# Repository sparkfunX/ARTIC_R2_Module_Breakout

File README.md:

# A Thing Plus Breakout for the ARGOS ARTIC R2 Castellated Module

**SPX-17855**

## Repository Contents

- [**/Hardware**](./Hardware) - Eagle PCB, SCH and LBR design files
- [**LICENSE.md**](./LICENSE,md) - contains the licence information

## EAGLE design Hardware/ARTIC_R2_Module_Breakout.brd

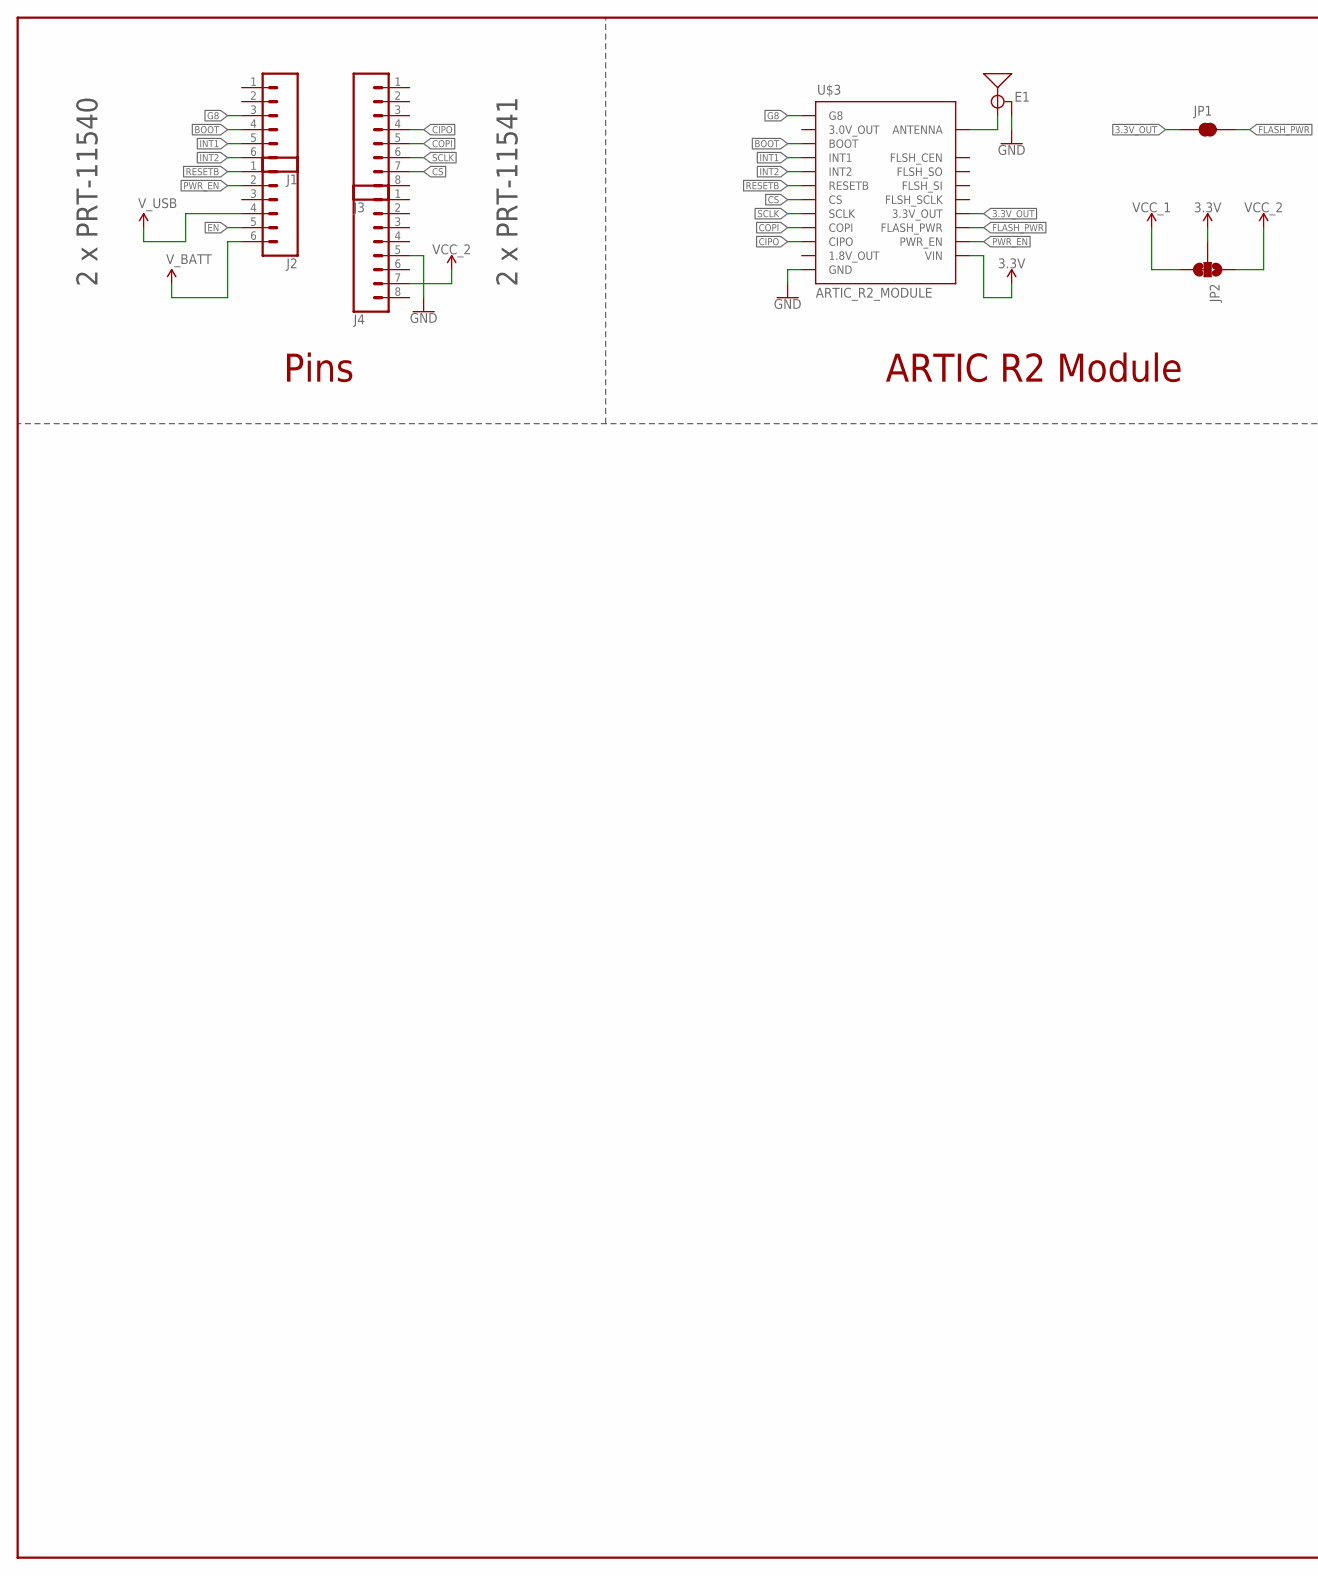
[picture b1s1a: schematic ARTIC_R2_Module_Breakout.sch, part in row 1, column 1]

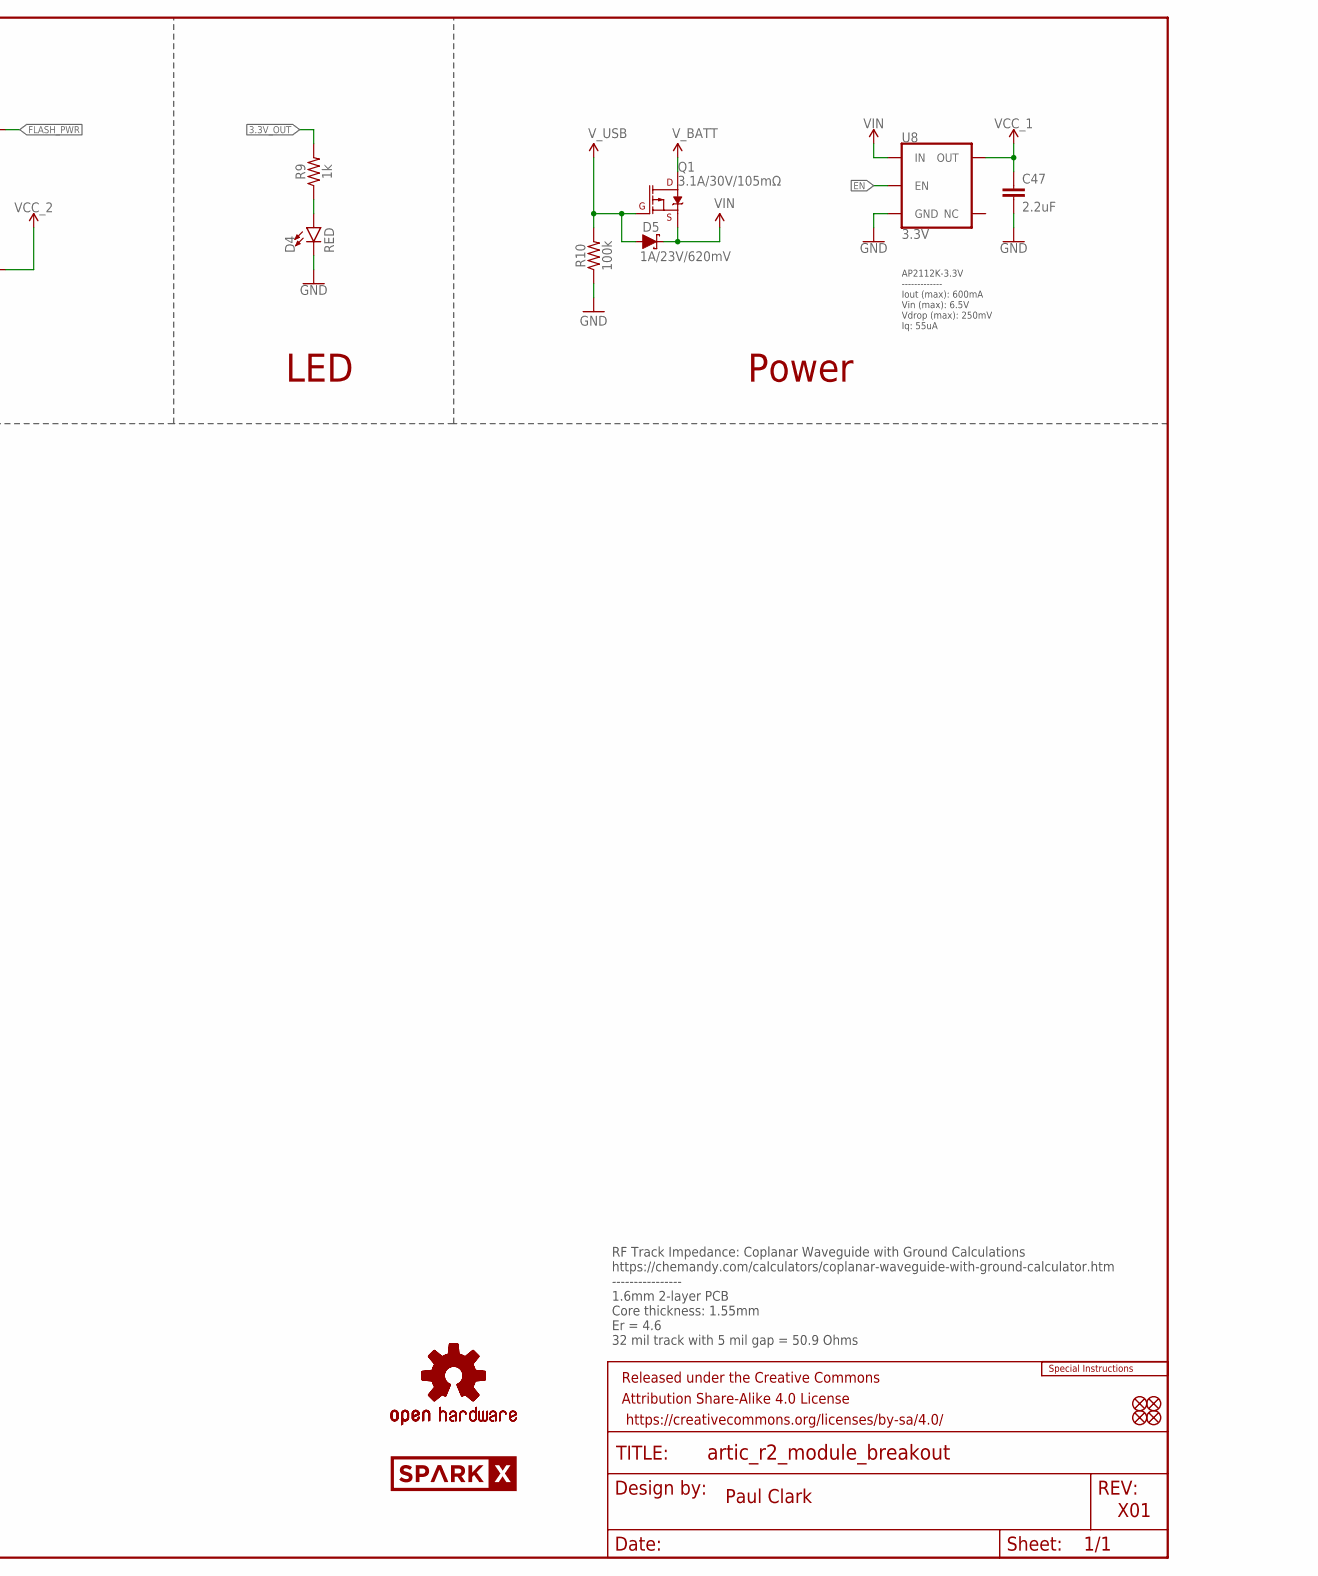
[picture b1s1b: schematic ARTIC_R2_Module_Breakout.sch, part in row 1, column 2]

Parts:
C47: 2.2uF; 0402-TIGHT
D4: RED; LED-0603
D5: 1A/23V/620mV; SOD-323
E1: ANTENNA-SMA-GROUNDEDEDGE_SMA_SMD; SMA-EDGE-SMD
FD1, FD2, FD3, FD4: FIDUCIAL1X2; FIDUCIAL-1X2
FRAME1: FRAME-LEDGER; CREATIVE_COMMONS
J1, J2: CONN_06SMD_MALE; 1X06_SMD_MALE
J3, J4: CONN_08SMD-MALE; 1X08_SMD_MALE
JP1: JUMPER-SMT_2_NC_TRACE_SILK; SMT-JUMPER_2_NC_TRACE_SILK
JP2: JUMPER-SMT_3_1-NC_TRACE_SILK; SMT-JUMPER_3_1-NC_TRACE_SILK
LOGO1: SPECIAL_INSTRUCTIONS-ORDERING; ORDERING_INSTRUCTIONS
LOGO2, LOGO3: OSHW-LOGOS; OSHW-LOGO-S
Q1: 3.1A/30V/105mΩ; SOT23-3
R9: 1k; 0402-TIGHT
R10: 100k; 0402-TIGHT
SPARKX2: SPARKX-LOGO4; SPARKX-MEDIUM
U8: 3.3V; SOT23-5
U$3: ARTIC_R2_MODULE

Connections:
3.3V: JP2.2, U$3.14 (VIN)
3.3V_OUT: JP1.1, R9.2, U$3.17 (3.3V_OUT)
ANTENNA: E1.SIG (SIGNAL), U$3.23 (ANTENNA)
BOOT: J1.4, U$3.3 (BOOT)
CIPO: J3.4, U$3.10 (CIPO)
COPI: J3.5, U$3.9 (COPI)
CS: J3.7, U$3.7 (CS)
EN: J2.5, U8.3 (EN)
FLASH_PWR: JP1.2, U$3.16 (FLASH_PWR)
G8: J1.3, U$3.1 (G8)
GND: C47.2, D4.C, E1.GND@0 (GND), E1.GND@1 (GND), J4.5, R10.1, U8.2 (GND), U$3.12 (GND), U$3.13 (GND), U$3.22 (GND), U$3.24 (GND)
INT1: J1.5, U$3.4 (INT1)
INT2: J1.6, U$3.5 (INT2)
unnamed: D4.A, R9.1
PWR_EN: J2.2, U$3.15 (PWR_EN)
RESETB: J2.1, U$3.6 (RESETB)
SCLK: J3.6, U$3.8 (SCLK)
VCC_1: C47.1, JP2.3, U8.5 (OUT)
VCC_2: J4.7, JP2.1
VIN: D5.C, Q1.2 (S), U8.1 (IN)
V_BATT: J2.6, Q1.3 (D)
V_USB: D5.A, J2.4, Q1.1 (G), R10.2

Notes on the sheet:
Paul Clark
X01
ARTIC R2 Module
Pins
RF Track Impedance: Coplanar Waveguide with Ground Calculations https://chemandy.com/calculators/coplanar-waveguide-with-ground-calculator.htm ---------------- 1.6mm 2-layer PCB Core thickness: 1.55mm Er = 4.6 32 mil track with 5 mil gap = 50.9 Ohms
LED
2 x PRT-11541
2 x PRT-11540
AP2112K-3.3V ------------- Iout (max): 600mA Vin (max): 6.5V Vdrop (max): 250mV Iq: 55uA
Power

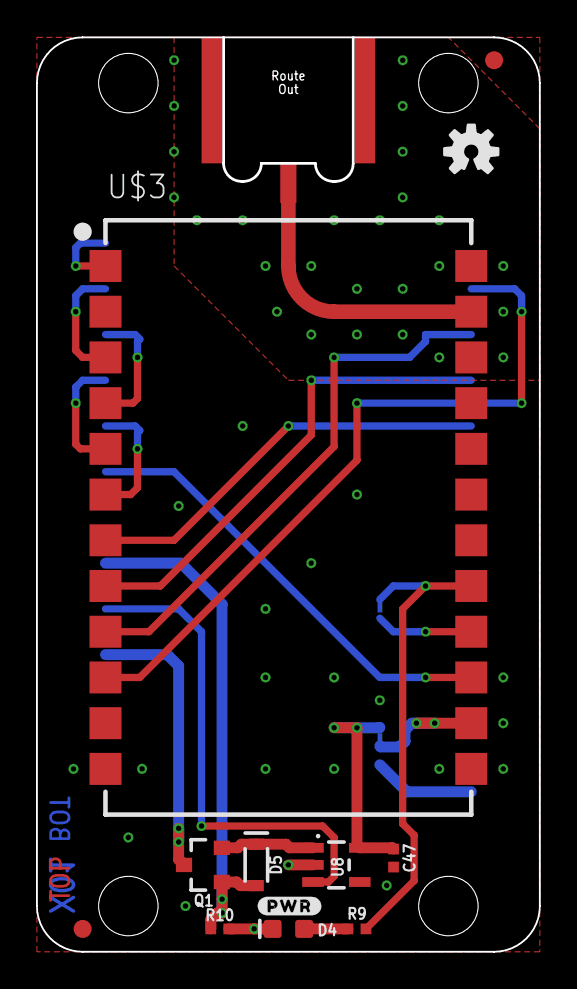
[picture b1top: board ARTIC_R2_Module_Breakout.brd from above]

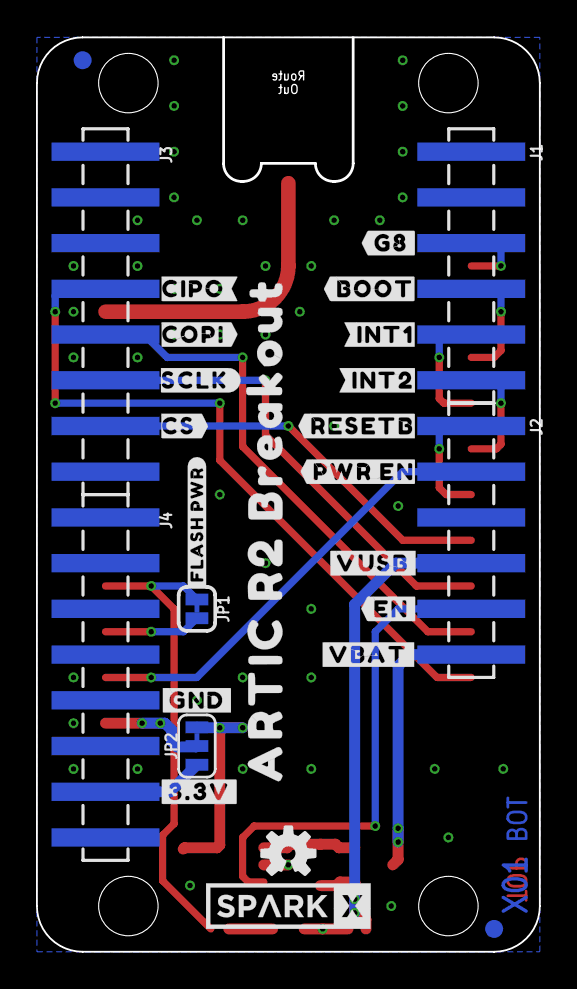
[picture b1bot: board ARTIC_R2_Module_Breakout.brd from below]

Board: 4 copper layers, 27.9 x 50.8 mm, 42 parts (27 on the bottom side), 22 nets.

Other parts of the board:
U$1: #GND#0
U$2: #3#3V#0
U$4: #FLASH_PWR#0
U$5: #VBAT#0
U$6: #G8#0
U$7: #EN#0
U$8: #VUSB#0
U$9: CIPO#0
U$12: COPI#0
U$14: SCLK#0
U$16: CS#0
U$18: #RESETB0
U$19: #PWR_EN0
U$24: #BOOT0
U$25: #INT10
U$26: #INT20
U$28: #PWR#0
U$29: ARTIC_R2_BREAKOUT0

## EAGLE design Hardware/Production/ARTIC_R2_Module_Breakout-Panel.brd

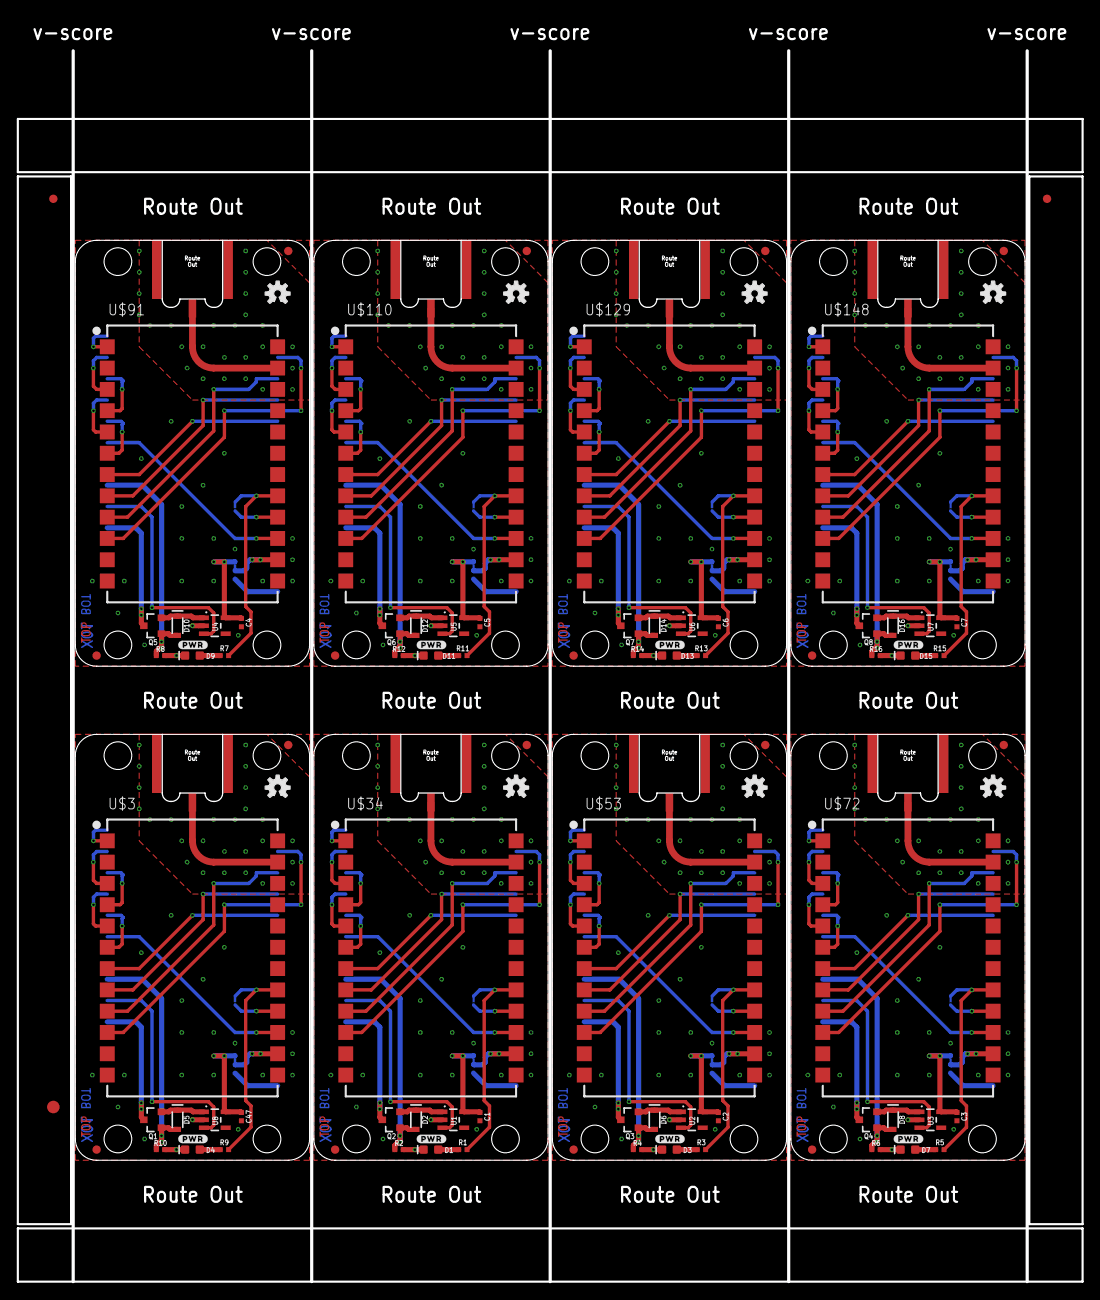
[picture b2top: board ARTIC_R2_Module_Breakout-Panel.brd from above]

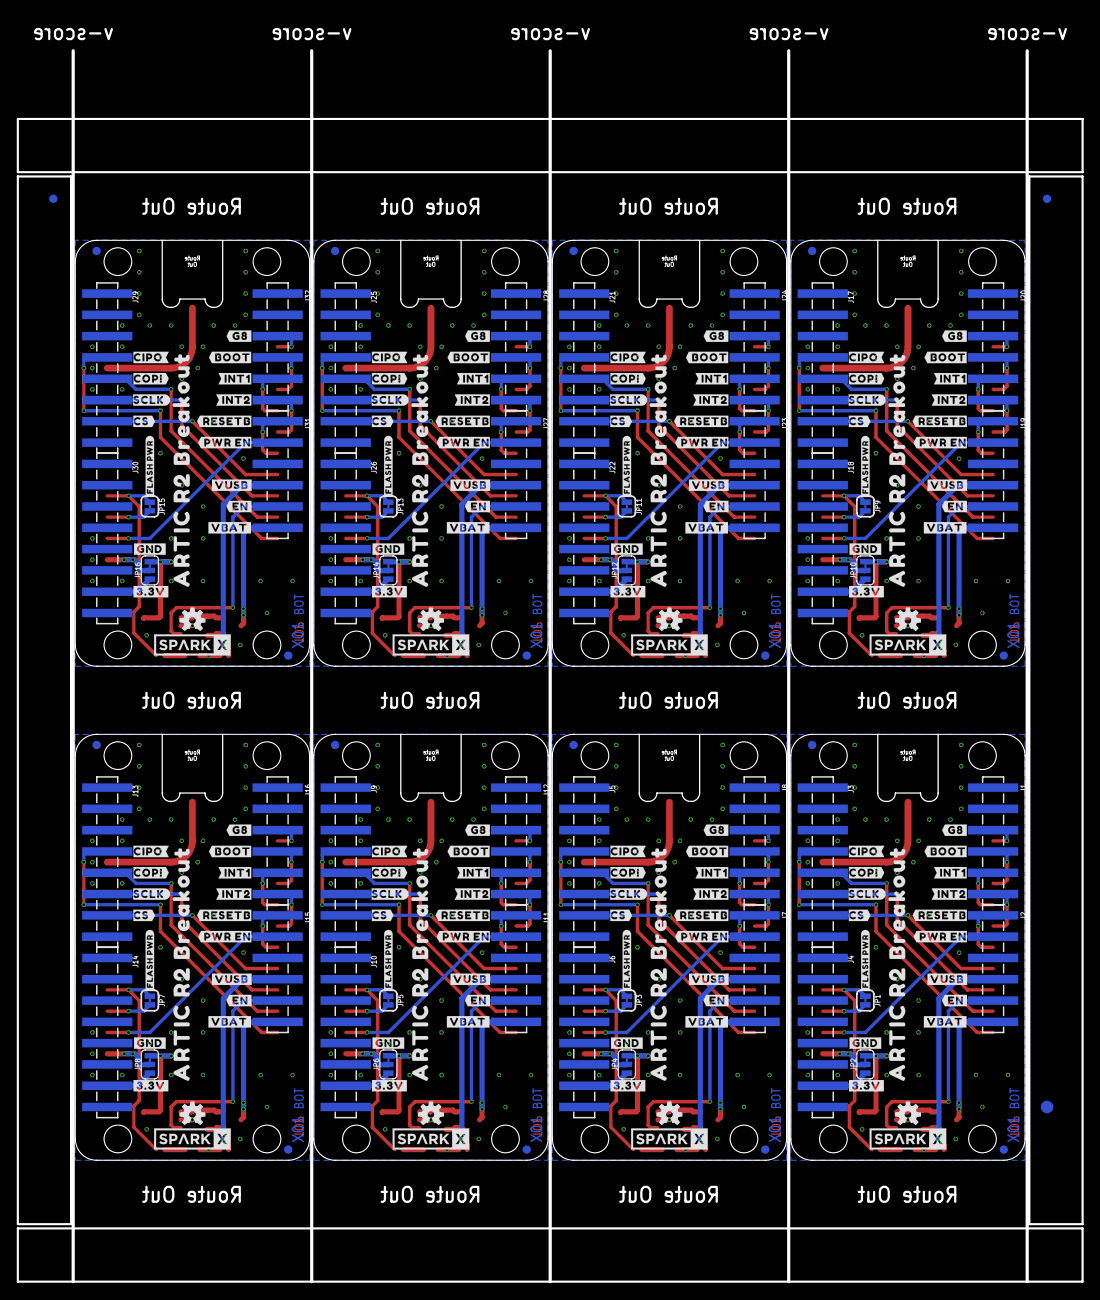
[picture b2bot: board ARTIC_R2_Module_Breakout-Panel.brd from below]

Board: 4 copper layers, 126.9 x 150.7 mm, 326 parts (219 on the bottom side), 176 nets.

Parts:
C1, C2, C3, C4, C5, C6, C7, C47: 2.2uF; 0402-TIGHT
D1, D3, D4, D7, D9, D11, D13, D15: RED; LED-0603
D2, D5, D6, D8, D10, D12, D14, D16: 1A/23V/620mV; SOD-323
E1, E2, E3, E4, E5, E6, E7, E8: ANTENNA-SMA-GROUNDEDEDGE_SMA_SMD; SMA-EDGE-SMD
E$1, E$2, E$3, E$4: FIDUCIAL-1X2
E$5, E$6: FIDUCIAL-1.5X3
FD1, FD2, FD3, FD4, FD5, FD6, FD7, FD8, FD9, FD10, FD11, FD12, FD13, FD14, FD15, FD16, FD17, FD18, FD19, FD20, FD21, FD22, FD23, FD24, FD25, FD26, FD27, FD28, FD29, FD30, FD31, FD32: FIDUCIAL1X2; FIDUCIAL-1X2
J1, J2, J7, J8, J11, J12, J15, J16, J19, J20, J23, J24, J27, J28, J31, J32: 1X06_SMD_MALE
J3, J4, J5, J6, J9, J10, J13, J14, J17, J18, J21, J22, J25, J26, J29, J30: 1X08_SMD_MALE
JP1, JP3, JP5, JP7, JP9, JP11, JP13, JP15: JUMPER-SMT_2_NC_TRACE_SILK; SMT-JUMPER_2_NC_TRACE_SILK
JP2, JP4, JP6, JP8, JP10, JP12, JP14, JP16: JUMPER-SMT_3_1-NC_TRACE_SILK; SMT-JUMPER_3_1-NC_TRACE_SILK
LOGO1, LOGO2, LOGO3, LOGO4, LOGO5, LOGO6, LOGO7, LOGO8, LOGO9, LOGO10, LOGO11, LOGO12, LOGO13, LOGO14, LOGO15, LOGO16: OSHW-LOGOS; OSHW-LOGO-S
Q1, Q2, Q3, Q4, Q5, Q6, Q7, Q8: 3.1A/30V/105mΩ; SOT23-3
R1, R3, R5, R7, R9, R11, R13, R15: 1k; 0402-TIGHT
R2, R4, R6, R8, R10, R12, R14, R16: 100k; 0402-TIGHT
SPARKX1, SPARKX2, SPARKX3, SPARKX4, SPARKX5, SPARKX6, SPARKX7, SPARKX8: SPARKX-LOGO4; SPARKX-MEDIUM
U1, U2, U3, U4, U5, U6, U7, U8: 3.3V; SOT23-5
U$1, U$32, U$51, U$70, U$89, U$108, U$127, U$146: #GND#0
U$2, U$33, U$52, U$71, U$90, U$109, U$128, U$147: #3#3V#0
U$3, U$34, U$53, U$72, U$91, U$110, U$129, U$148: ARTIC_R2_MODULE
U$4, U$38, U$57, U$76, U$95, U$114, U$133, U$152: #FLASH_PWR#0
U$5, U$35, U$54, U$73, U$92, U$111, U$130, U$149: #VBAT#0
U$6, U$31, U$50, U$69, U$88, U$107, U$126, U$145: #G8#0
U$7, U$36, U$55, U$74, U$93, U$112, U$131, U$150: #EN#0
U$8, U$37, U$56, U$75, U$94, U$113, U$132, U$151: #VUSB#0
U$9, U$10, U$39, U$58, U$77, U$96, U$115, U$134: CIPO#0
U$11, U$12, U$40, U$59, U$78, U$97, U$116, U$135: COPI#0
U$13, U$14, U$41, U$60, U$79, U$98, U$117, U$136: SCLK#0
U$15, U$16, U$42, U$61, U$80, U$99, U$118, U$137: CS#0
U$17, U$24, U$43, U$62, U$81, U$100, U$119, U$138: #BOOT0
U$18, U$20, U$44, U$63, U$82, U$101, U$120, U$139: #RESETB0
U$19, U$21, U$45, U$64, U$83, U$102, U$121, U$140: #PWR_EN0
U$22, U$26, U$46, U$65, U$84, U$103, U$122, U$141: #INT20
U$23, U$25, U$47, U$66, U$85, U$104, U$123, U$142: #INT10
U$27, U$28, U$48, U$67, U$86, U$105, U$124, U$143: #PWR#0
U$29, U$30, U$49, U$68, U$87, U$106, U$125, U$144: ARTIC_R2_BREAKOUT0

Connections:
3.3V: JP2.2, U$3.14
3.3V1: JP4.2, U$34.14
3.3V2: JP6.2, U$53.14
3.3V3: JP8.2, U$72.14
3.3V4: JP10.2, U$91.14
3.3V5: JP12.2, U$110.14
3.3V6: JP14.2, U$129.14
3.3V7: JP16.2, U$148.14
3.3V_OUT: JP1.1, R9.2, U$3.17
3.3V_OUT1: JP3.1, R1.2, U$34.17
3.3V_OUT2: JP5.1, R3.2, U$53.17
3.3V_OUT3: JP7.1, R5.2, U$72.17
3.3V_OUT4: JP9.1, R7.2, U$91.17
3.3V_OUT5: JP11.1, R11.2, U$110.17
3.3V_OUT6: JP13.1, R13.2, U$129.17
3.3V_OUT7: JP15.1, R15.2, U$148.17
ANTENNA: E1.SIG, U$3.23
ANTENNA1: E2.SIG, U$34.23
ANTENNA2: E3.SIG, U$53.23
ANTENNA3: E4.SIG, U$72.23
ANTENNA4: E5.SIG, U$91.23
ANTENNA5: E6.SIG, U$110.23
ANTENNA6: E7.SIG, U$129.23
ANTENNA7: E8.SIG, U$148.23
BOOT: J1.4, U$3.3
BOOT1: J8.4, U$34.3
BOOT2: J12.4, U$53.3
BOOT3: J16.4, U$72.3
BOOT4: J20.4, U$91.3
BOOT5: J24.4, U$110.3
BOOT6: J28.4, U$129.3
BOOT7: J32.4, U$148.3
CIPO: J3.4, U$3.10
CIPO1: J5.4, U$34.10
CIPO2: J9.4, U$53.10
CIPO3: J13.4, U$72.10
CIPO4: J17.4, U$91.10
CIPO5: J21.4, U$110.10
CIPO6: J25.4, U$129.10
CIPO7: J29.4, U$148.10
COPI: J3.5, U$3.9
COPI1: J5.5, U$34.9
COPI2: J9.5, U$53.9
COPI3: J13.5, U$72.9
COPI4: J17.5, U$91.9
COPI5: J21.5, U$110.9
COPI6: J25.5, U$129.9
COPI7: J29.5, U$148.9
CS: J3.7, U$3.7
CS1: J5.7, U$34.7
CS2: J9.7, U$53.7
CS3: J13.7, U$72.7
CS4: J17.7, U$91.7
CS5: J21.7, U$110.7
CS6: J25.7, U$129.7
CS7: J29.7, U$148.7
EN: J2.5, U8.3
EN1: J7.5, U1.3
EN2: J11.5, U2.3
EN3: J15.5, U3.3
EN4: J19.5, U4.3
EN5: J23.5, U5.3
EN6: J27.5, U6.3
EN7: J31.5, U7.3
FLASH_PWR: JP1.2, U$3.16
FLASH_PWR1: JP3.2, U$34.16
FLASH_PWR2: JP5.2, U$53.16
FLASH_PWR3: JP7.2, U$72.16
FLASH_PWR4: JP9.2, U$91.16
FLASH_PWR5: JP11.2, U$110.16
FLASH_PWR6: JP13.2, U$129.16
FLASH_PWR7: JP15.2, U$148.16
G1: J8.3, U$34.1
G2: J12.3, U$53.1
G3: J16.3, U$72.1
G4: J20.3, U$91.1
G5: J24.3, U$110.1
G6: J28.3, U$129.1
G7: J32.3, U$148.1
G8: J1.3, U$3.1
GND: C47.2, D4.C, E1.GND@0, E1.GND@1, J4.5, R10.1, U8.2, U$3.12, U$3.13, U$3.22, U$3.24
GND1: C1.2, D1.C, E2.GND@0, E2.GND@1, J6.5, R2.1, U1.2, U$34.12, U$34.13, U$34.22, U$34.24
GND2: C2.2, D3.C, E3.GND@0, E3.GND@1, J10.5, R4.1, U2.2, U$53.12, U$53.13, U$53.22, U$53.24
GND3: C3.2, D7.C, E4.GND@0, E4.GND@1, J14.5, R6.1, U3.2, U$72.12, U$72.13, U$72.22, U$72.24
GND4: C4.2, D9.C, E5.GND@0, E5.GND@1, J18.5, R8.1, U4.2, U$91.12, U$91.13, U$91.22, U$91.24
GND5: C5.2, D11.C, E6.GND@0, E6.GND@1, J22.5, R12.1, U5.2, U$110.12, U$110.13, U$110.22, U$110.24
GND6: C6.2, D13.C, E7.GND@0, E7.GND@1, J26.5, R14.1, U6.2, U$129.12, U$129.13, U$129.22, U$129.24
GND7: C7.2, D15.C, E8.GND@0, E8.GND@1, J30.5, R16.1, U7.2, U$148.12, U$148.13, U$148.22, U$148.24
INT1: J1.5, U$3.4
INT2: J1.6, U$3.5
INT3: J8.6, U$34.5
INT4: J8.5, U$34.4
INT5: J12.6, U$53.5
INT6: J12.5, U$53.4
INT7: J16.6, U$72.5
INT8: J16.5, U$72.4
INT9: J20.6, U$91.5
INT10: J20.5, U$91.4
INT11: J24.6, U$110.5
INT12: J24.5, U$110.4
INT13: J28.6, U$129.5
INT14: J28.5, U$129.4
INT15: J32.6, U$148.5
INT16: J32.5, U$148.4
unnamed: D1.A, R1.1
unnamed: D3.A, R3.1
unnamed: D7.A, R5.1
unnamed: D9.A, R7.1
unnamed: D11.A, R11.1
unnamed: D13.A, R13.1
unnamed: D15.A, R15.1
unnamed: D4.A, R9.1
PWR_EN: J2.2, U$3.15
PWR_EN1: J7.2, U$34.15
PWR_EN2: J11.2, U$53.15
PWR_EN3: J15.2, U$72.15
PWR_EN4: J19.2, U$91.15
PWR_EN5: J23.2, U$110.15
PWR_EN6: J27.2, U$129.15
PWR_EN7: J31.2, U$148.15
RESETB: J2.1, U$3.6
RESETB1: J7.1, U$34.6
RESETB2: J11.1, U$53.6
RESETB3: J15.1, U$72.6
RESETB4: J19.1, U$91.6
RESETB5: J23.1, U$110.6
RESETB6: J27.1, U$129.6
RESETB7: J31.1, U$148.6
SCLK: J3.6, U$3.8
SCLK1: J5.6, U$34.8
SCLK2: J9.6, U$53.8
SCLK3: J13.6, U$72.8
SCLK4: J17.6, U$91.8
SCLK5: J21.6, U$110.8
SCLK6: J25.6, U$129.8
SCLK7: J29.6, U$148.8
VCC_1: C47.1, JP2.3, U8.5
VCC_2: J4.7, JP2.1
VCC_3: C1.1, JP4.3, U1.5
VCC_4: J6.7, JP4.1
VCC_5: C2.1, JP6.3, U2.5
VCC_6: J10.7, JP6.1
VCC_7: C3.1, JP8.3, U3.5
VCC_8: J14.7, JP8.1
VCC_9: C4.1, JP10.3, U4.5
VCC_10: J18.7, JP10.1
VCC_11: C5.1, JP12.3, U5.5
VCC_12: J22.7, JP12.1
VCC_13: C6.1, JP14.3, U6.5
VCC_14: J26.7, JP14.1
VCC_15: C7.1, JP16.3, U7.5
VCC_16: J30.7, JP16.1
VIN: D5.C, Q1.2, U8.1
VIN1: D2.C, Q2.2, U1.1
VIN2: D6.C, Q3.2, U2.1
VIN3: D8.C, Q4.2, U3.1
VIN4: D10.C, Q5.2, U4.1
VIN5: D12.C, Q6.2, U5.1
VIN6: D14.C, Q7.2, U6.1
VIN7: D16.C, Q8.2, U7.1
V_BATT: J2.6, Q1.3
V_BATT1: J7.6, Q2.3
V_BATT2: J11.6, Q3.3
V_BATT3: J15.6, Q4.3
V_BATT4: J19.6, Q5.3
V_BATT5: J23.6, Q6.3
V_BATT6: J27.6, Q7.3
V_BATT7: J31.6, Q8.3
V_USB: D5.A, J2.4, Q1.1, R10.2
V_USB1: D2.A, J7.4, Q2.1, R2.2
V_USB2: D6.A, J11.4, Q3.1, R4.2
V_USB3: D8.A, J15.4, Q4.1, R6.2
V_USB4: D10.A, J19.4, Q5.1, R8.2
V_USB5: D12.A, J23.4, Q6.1, R12.2
V_USB6: D14.A, J27.4, Q7.1, R14.2
V_USB7: D16.A, J31.4, Q8.1, R16.2

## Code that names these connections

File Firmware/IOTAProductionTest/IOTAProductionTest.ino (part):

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  ** This code has only been tested using v1.2.1 of the Apollo3 Boards **
  ** Set the Board to "SparkFun Artemis Thing Plus" **
  
  Connect an antenna, press the IOTA gently onto the Test Jig spring pins, then click "GO" to begin.
  
  Helpful messages will appear in the Serial Monitor (115200 Baud) as the test progresses.
  
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  CS_Pin = A5 (D24)
  GAIN8_Pin = D3
  BOOT_Pin = D4
  INT1_Pin = D5
  INT2_Pin = D6
  RESET_Pin = D7
  IOTA_PWR_EN_Pin = D8
  (SPI COPI = D11)
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int CS_Pin = 24;
int GAIN8_Pin = 3; // Optional. Set to -1 if you don't want to control the gain. The library defaults to maximum power.
int BOOT_Pin = 4;
int INT1_Pin = 5;
int INT2_Pin = 6;
int RESET_Pin = 7;
int IOTA_PWR_EN_Pin = 8;

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  
  pinMode(GO, INPUT_PULLUP); // Configure the GO button

  pinMode(INT1_Pin, INPUT);
  pinMode(INT2_Pin, INPUT);

  pinMode(GAIN8_Pin, OUTPUT);
  pinMode(BOOT_Pin, OUTPUT);
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      Serial.println(F("Test 3 Step 1: Starting the ARTIC R2..."));
    
      // Begin the ARTIC: enable power and boot from flash
      if (myARTIC.beginIOTA(CS_Pin, RESET_Pin, BOOT_Pin, IOTA_PWR_EN_Pin, INT1_Pin, INT2_Pin, GAIN8_Pin) == false)
      {
        Serial.println("Test 3 Step 1: ARTIC R2 not detected!");
        fail();
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
      delay(100);

      if (digitalRead(INT2_Pin) != LOW)
      {
        Serial.println("Test 4 Step 7: INT2_Pin is not low!");
        fail();
      }      

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    
      if (status.STATUS_REGISTER_BITS.DSP2MCU_INT2) // Check the interrupt 2 flag. This will go high if satellite detection times out
      {
        Serial.println(F("Test 5 Step 2: INT2 pin is high. Satellite detection has timed out!"));
      }
      else if (status.STATUS_REGISTER_BITS.DSP2MCU_INT1) // Check the interrupt 1 flag. This will go high when a satellite is detected
      {
        Serial.println(F("Test 5 Step 3: INT1 pin is high. Satellite detected!"));
        fail(); // This should be impossible indoors?!
#ifdef noFail
        loop_step = ARTIC_TX; // Move on
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      {
        Serial.println(F("Test 5: RX is complete!"));

        if (digitalRead(INT2_Pin) != HIGH)
        {
          Serial.println("Test 5 Step 4: INT2_Pin is not high!");
          fail();
#ifdef noFail
          loop_step = ARTIC_TX; // Move on
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
      delay(100);

      if (digitalRead(INT1_Pin) != LOW)
      {
        Serial.println("Test 6 Step 3: INT1_Pin is not low!");
        fail();
      }

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
      if (status.STATUS_REGISTER_BITS.DSP2MCU_INT1) // Check the interrupt 1 flag. This will go high when TX is finished
      {
        Serial.println(F("Test 7 Step 2: INT1 pin is high. TX is finished (or MCU is in IDLE_STATE)!"));
      }

      if (status.STATUS_REGISTER_BITS.DSP2MCU_INT2) // Check the interrupt 2 flag. This will go high when if the message was invalid
      {
        Serial.println(F("Test 7 Step 3: INT2 pin is high. TX message was invalid! (Something really bad must have happened...)"));
        fail();
        loop_step = tests_complete; // We're done
      }
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      {
        Serial.println(F("Test 7: Transmission is complete!"));

        if (digitalRead(INT1_Pin) != HIGH)
        {
          Serial.println("Test 7 Step 4: INT1_Pin is not high!");
          fail();
        }

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
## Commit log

2020-12-18 Final tweaks
2021-01-12 Updates to match the revised module design
2021-02-04 Adding a note of the SKU

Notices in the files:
Firmware/IOTAProductionTest/IOTAProductionTest.ino:
License: please see the license file at:
https://github.com/sparkfun/SparkFun_ARGOS_ARTIC_R2_Arduino_Library/LICENSE.md
parts and their libraries:
SparkFun-Aesthetics: Licensing: Creative Commons ShareAlike 4.0 International - https://creativecommons.org/licenses/by-sa/4.0
SparkFun-Aesthetics: Released under the Creative Commons Attribution Share-Alike 4.0 License
SparkFun-Aesthetics: https://creativecommons.org/licenses/by-sa/4.0
